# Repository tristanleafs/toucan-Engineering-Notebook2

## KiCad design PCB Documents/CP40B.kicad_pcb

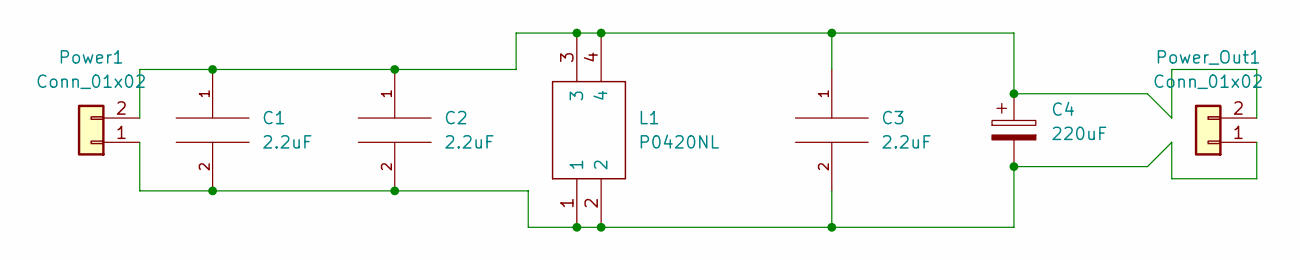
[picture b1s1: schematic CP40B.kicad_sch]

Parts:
C1, C2, C3: 2.2uF; CAPC2012X145N
C4: 220uF; CAPPA7250W80L3050D1050
L1: P0420NL; P0420NLT; Mouser Part Number 673-P0420NL
Power1: Conn_01x02; JST_VH_B2P-VH-B_1x02_P3.96mm_Vertical
Power_Out1: Conn_01x02; JST_VH_B2P-VH_1x02_P3.96mm_Vertical

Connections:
unnamed: C1.1, C2.1, C3.1, C4.1, L1.3, L1.4, Power1.2, Power_Out1.2
unnamed: C1.2, C2.2, C3.2, C4.2, L1.1, L1.2, Power1.1, Power_Out1.1

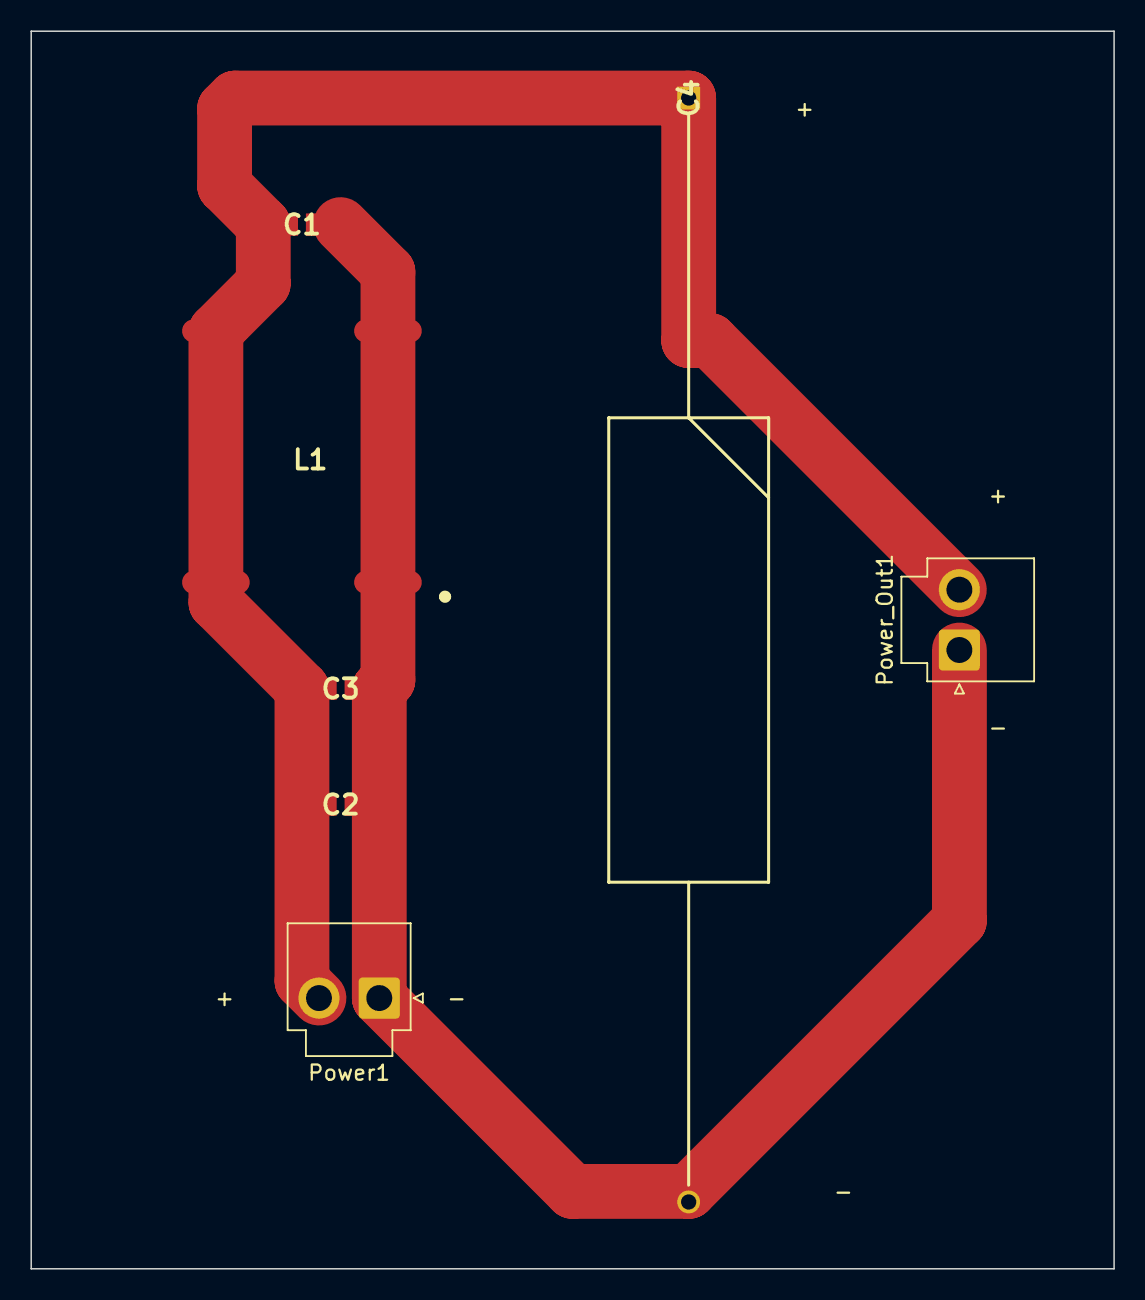
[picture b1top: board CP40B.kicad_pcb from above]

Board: 2 copper layers, 71.1 x 81.3 mm, 7 parts (0 on the bottom side), 2 nets.
